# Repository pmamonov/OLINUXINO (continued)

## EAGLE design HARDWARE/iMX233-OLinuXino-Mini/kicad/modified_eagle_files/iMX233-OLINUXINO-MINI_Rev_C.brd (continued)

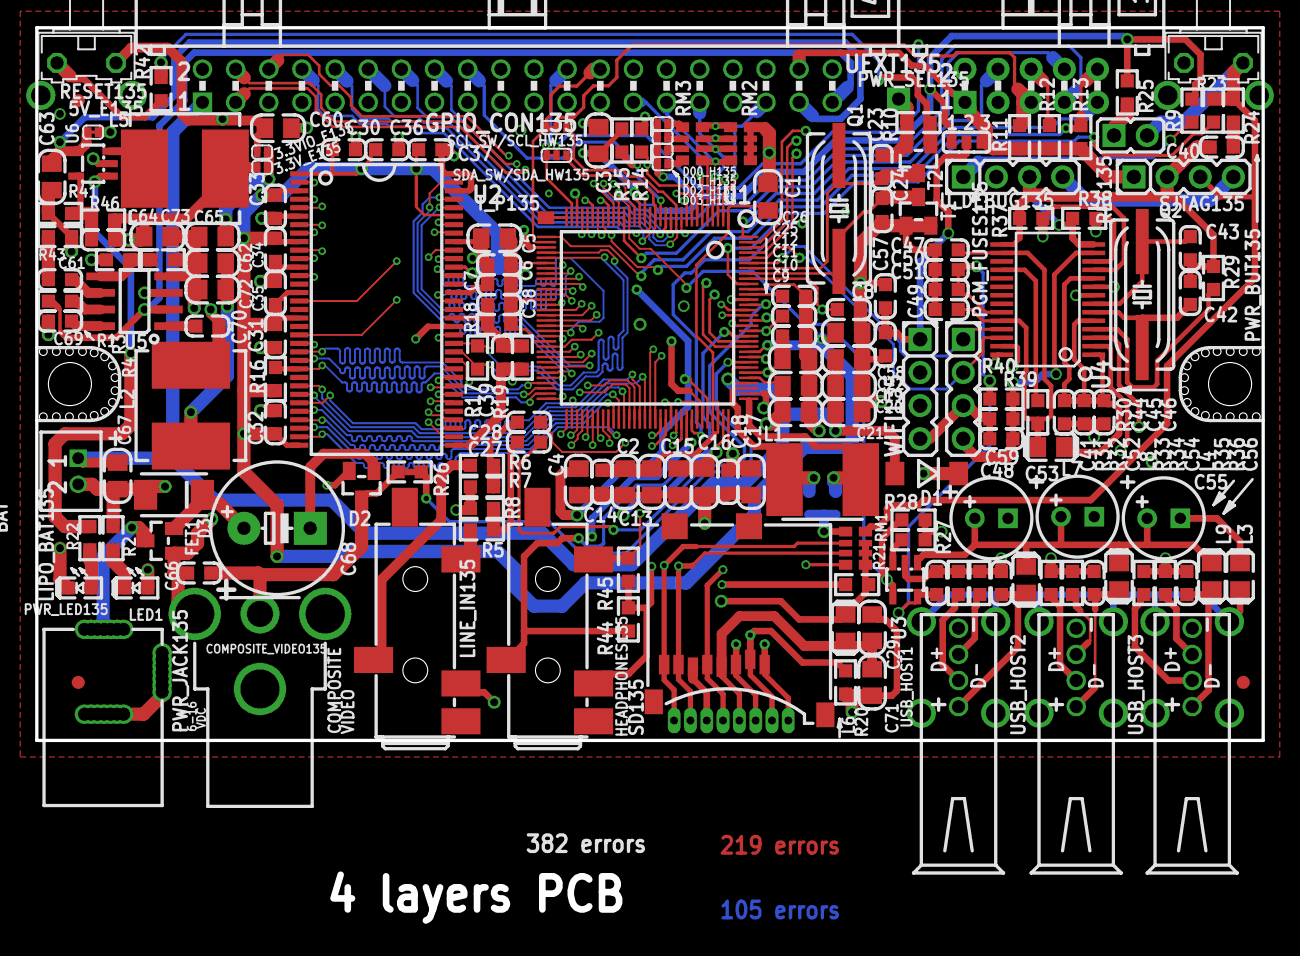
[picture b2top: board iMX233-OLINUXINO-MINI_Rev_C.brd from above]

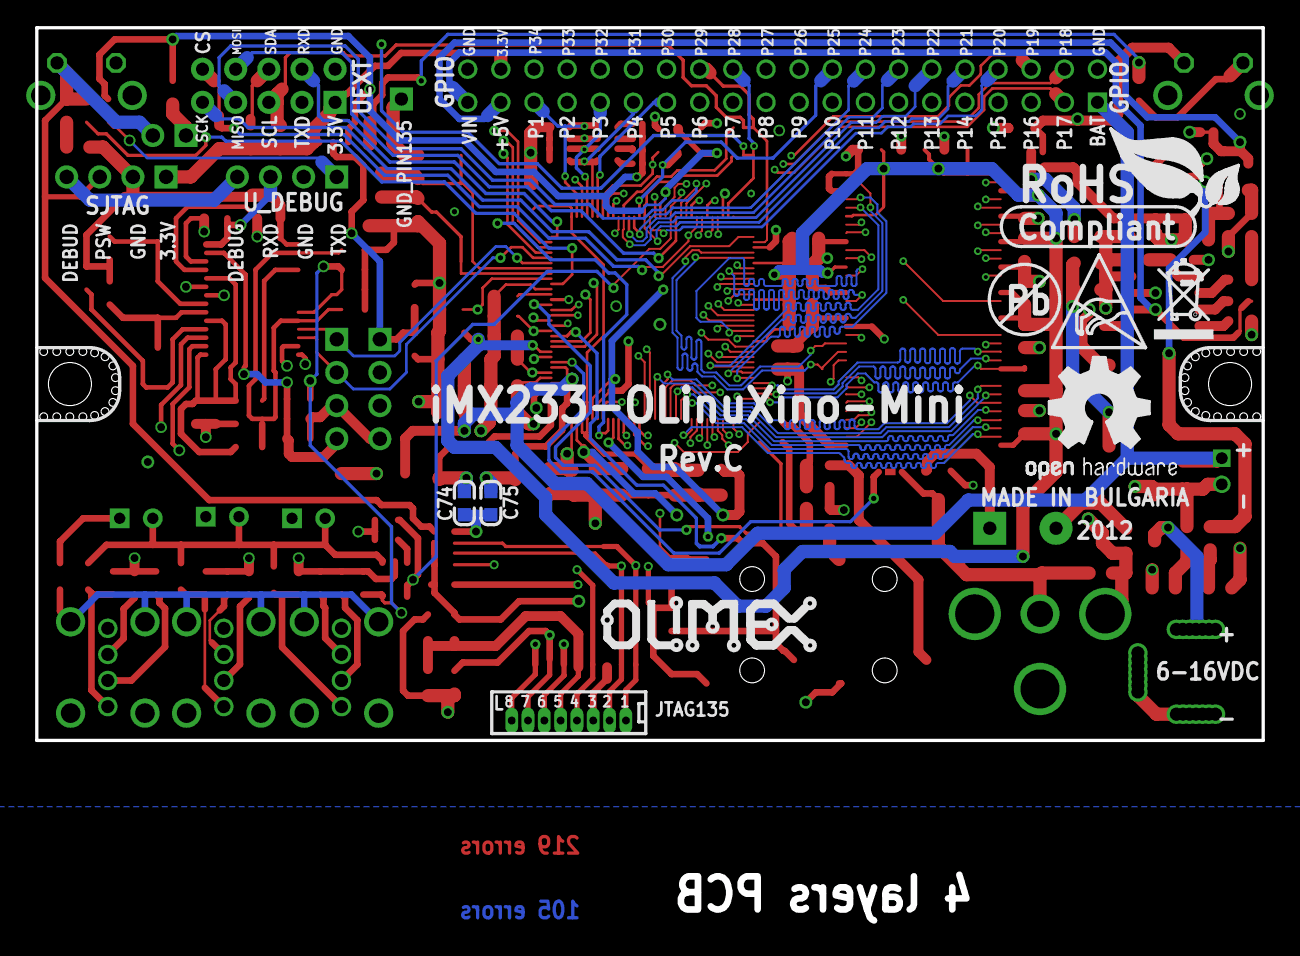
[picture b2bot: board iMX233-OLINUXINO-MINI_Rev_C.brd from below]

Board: 4 copper layers, 94.0 x 54.6 mm, 190 parts (10 on the bottom side), 170 nets.

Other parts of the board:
U$5: LOGO-OPENHARDWARE_8X8
U$6: JM42_PACTEC-101X61X25_MILLED
U$8: OLIMEX1_V
U$9: PB
U$10: ESD_SYMBOL
U$11: RECYCLE_BIN1/8
U$12: ROHS

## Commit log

2015-11-22 HARDWARE: iMX233-OLinuXino-Mini: convert project to the kicad format
2015-11-22 HARDWARE: iMX233-OLinuXino-NANO: convert project to the kicad format
    N.B.: Orphaned GNDs!
